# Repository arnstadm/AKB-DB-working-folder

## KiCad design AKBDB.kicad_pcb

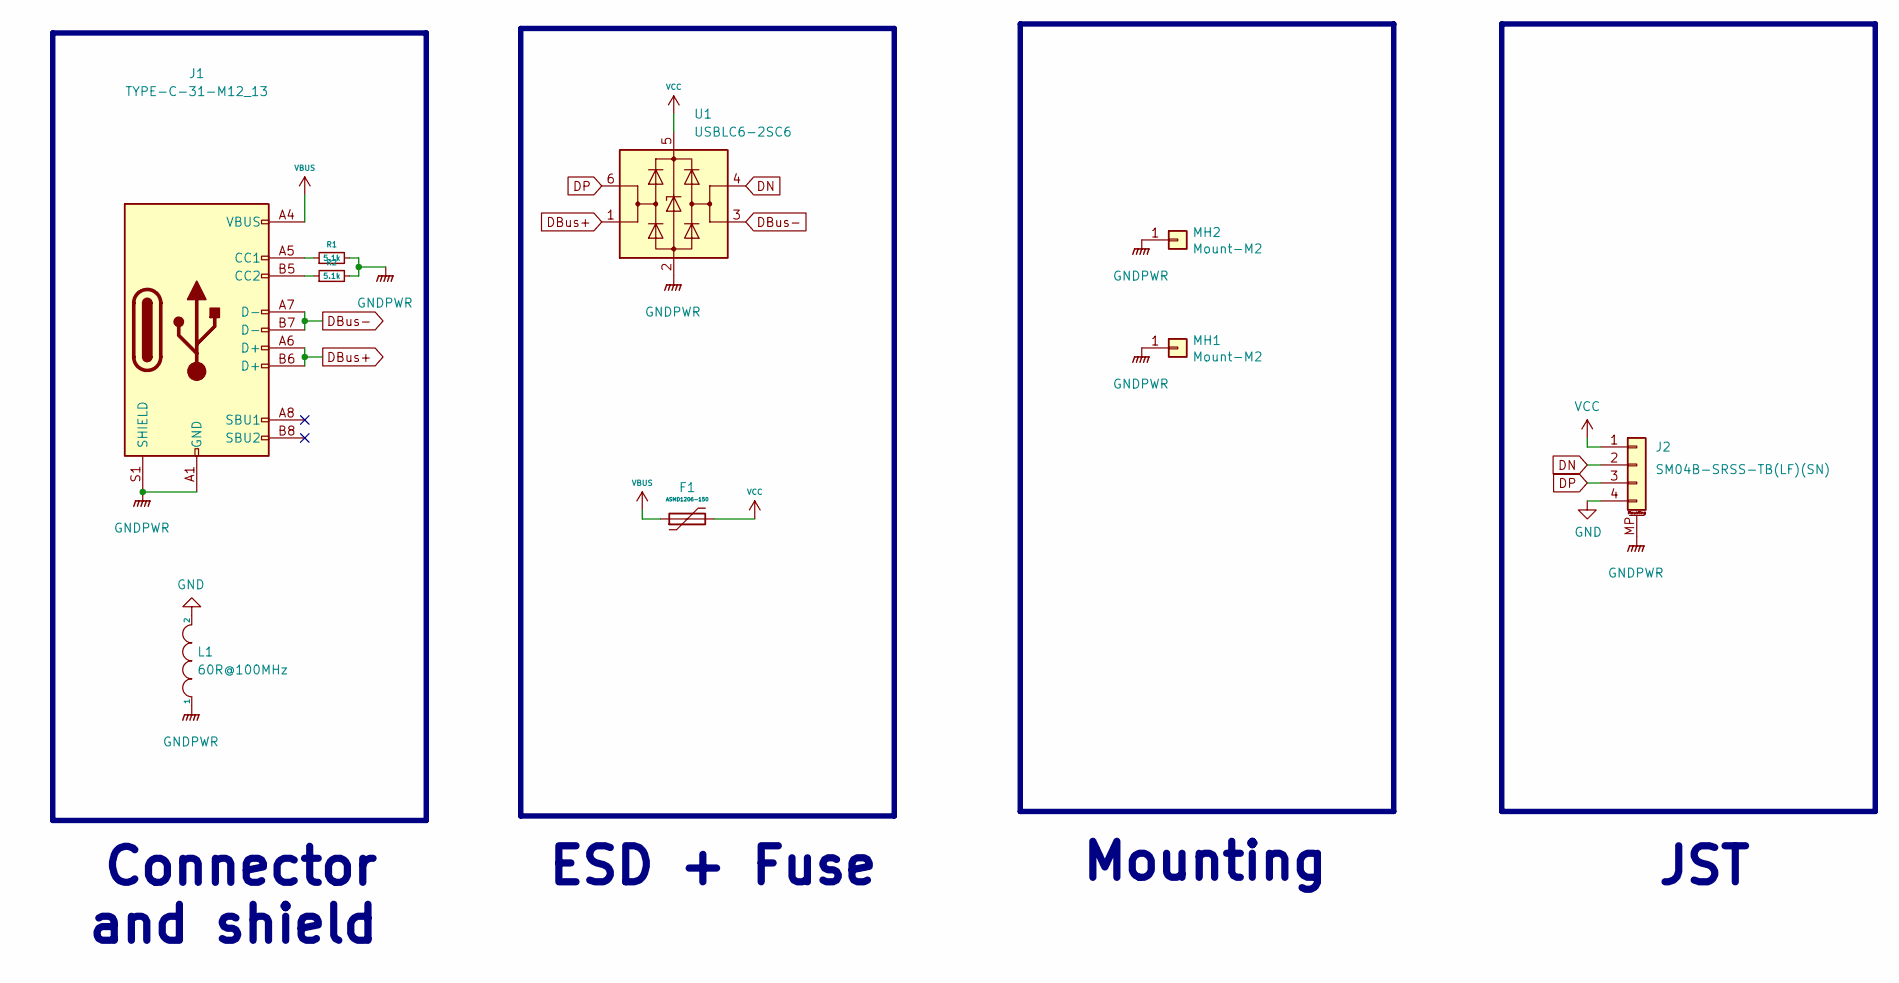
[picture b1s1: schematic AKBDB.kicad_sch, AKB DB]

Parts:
F1: ASMD1206-150; Fuse_0603_1608Metric; Manufacturer Part No ASMD1206-150; LCSC Part No C135342
J1: TYPE-C-31-M12_13; USB_C_Receptacle_HRO_TYPE-C-31-M-12; Manufacturer Part No TYPE-C-31-M-12; LCSC Part No C165948
J2: SM04B-SRSS-TB(LF)(SN); JST_SH_SM04B-SRSS-TB_1x04-1MP_P1.00mm_Horizontal; Manufacturer Part No SM04B-SRSS-TB(LF)(SN); LCSC Part No C160404
L1: 60R@100MHz; L_0603_1608Metric
MH1, MH2: Mount-M2; Generic-Mounthole
R1, R2: 5.1k; R_0402_1005Metric
U1: USBLC6-2SC6; SOT-23-6

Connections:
DBus+: J1.A6 (D+), J1.B6 (D+), U1.1 (I/O1)
DBus-: J1.A7 (D-), J1.B7 (D-), U1.3 (I/O2)
DN: J2.2, U1.4 (I/O2)
DP: J2.3, U1.6 (I/O1)
GND: J2.4, L1.2
GNDPWR: J1.A1 (GND), J1.A12 (GND), J1.B1 (GND), J1.B12 (GND), J1.S1 (SHIELD), J2.MP (MountPin), L1.1, MH1.1, MH2.1, R1.2, R2.2, U1.2 (GND)
unnamed: J1.A5 (CC1), R1.1
unnamed: J1.B5 (CC2), R2.1
VBUS: F1.1, J1.A4 (VBUS), J1.A9 (VBUS), J1.B4 (VBUS), J1.B9 (VBUS)
VCC: F1.2, J2.1, U1.5 (VBUS)

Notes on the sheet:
Mounting
Connector and shield
ESD + Fuse
JST

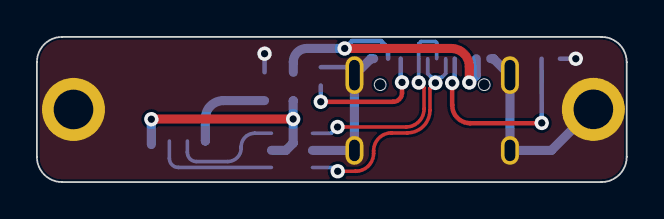
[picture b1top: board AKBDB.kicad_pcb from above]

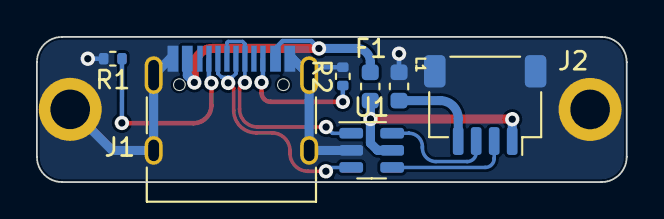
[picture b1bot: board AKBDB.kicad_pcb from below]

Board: 2 copper layers, 32.8 x 8.1 mm, 9 parts (7 on the bottom side), 10 nets.

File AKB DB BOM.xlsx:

Comment | Designator | Footprint | LCSC
ASMD1206-150 | F1 | Fuse:Fuse_0603_1608Metric | C207011
TYPE-C-31-M12_13 | J1 | logo:USB_C_Receptacle_HRO_TYPE-C-31-M-12 | C319148
SM04B-SRSS-TB(LF)(SN) | J2 | logo:JST_SH_SM04B-SRSS-TB_1x04-1MP_P1.00mm_Horizontal | C145956
60R@100MHz | L1 | Inductor_SMD:L_0603_1608Metric | C88985
5.1k | R1,R2 | Resistor_SMD:R_0402_1005Metric | C25905
USBLC6-2SC6 | U3 | Package_TO_SOT_SMD:SOT-23-6 | C2827654

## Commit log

2022-05-23 small fixes
2022-05-23 slight adjustments to the datalines
2022-05-23 Added fabrication files
